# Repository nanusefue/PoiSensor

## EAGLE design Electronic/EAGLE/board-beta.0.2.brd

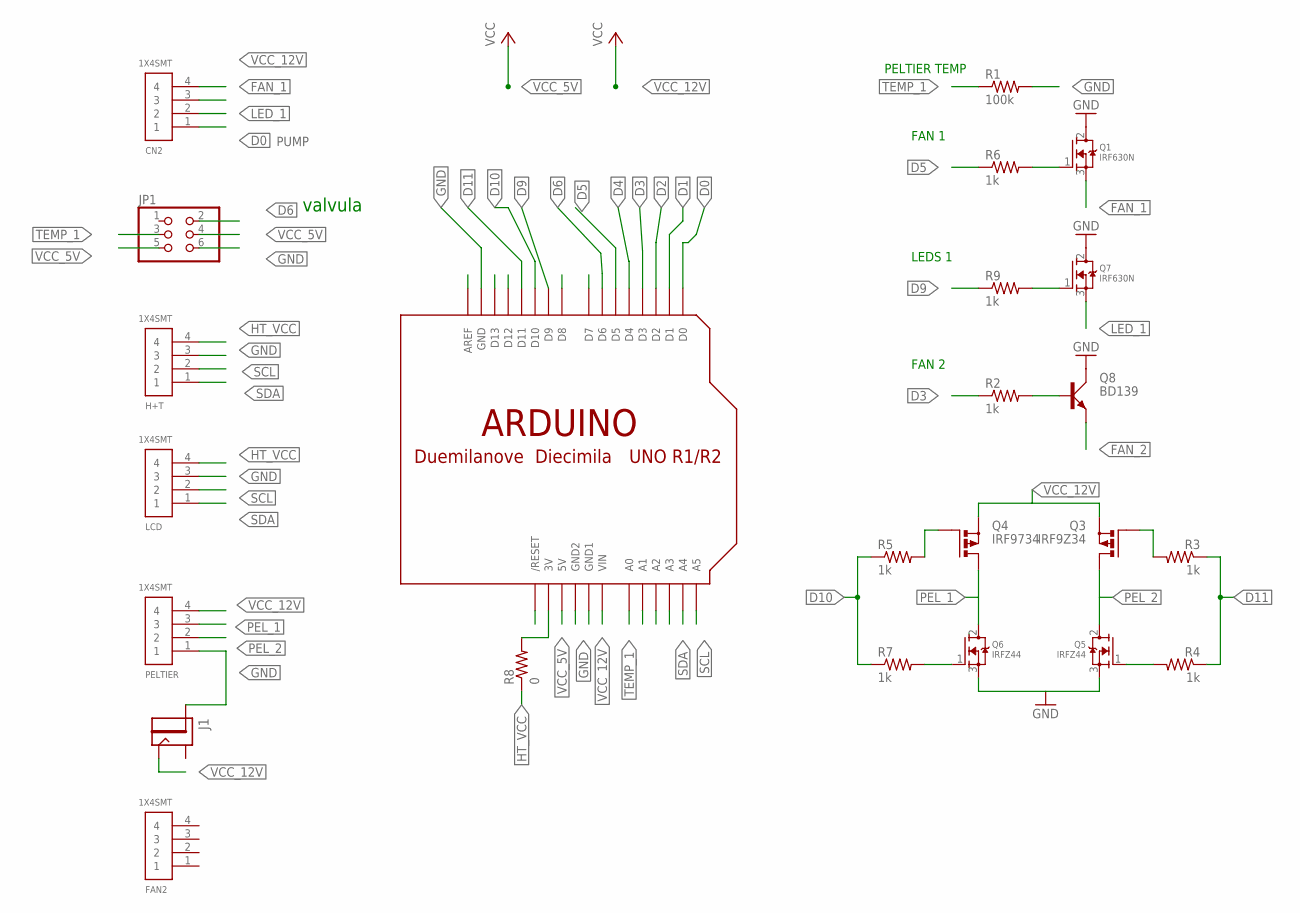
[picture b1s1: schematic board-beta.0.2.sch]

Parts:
CN2: 1X4SMT; 1X4-SMT
FAN2: 1X4SMT; 1X4-SMT
H+T: 1X4SMT; 1X4-SMT
J1: JACK2.1MM; JACK_2.1MM
JP1: PINHD-2X3-SMD; 2X03SMD
LCD: 1X4SMT; 1X4-SMT
PELTIER: 1X4SMT; 1X4-SMT
Q1, Q7: IRF630N; TO220V
Q3: IRF9Z34; TO220BV
Q4: IRF9734; TO220BV
Q5, Q6: IRFZ44; TO220V
Q8: BD139; TO126AV
R1: 100k; R1206FAB
R2, R3, R4, R5, R6, R7, R9: 1k; R1206FAB
R8: 0; R1206FAB
U$1: ARDUINOUNO; ARDUINO

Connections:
D0: CN2.1, U$1.D0
D1: U$1.D1
D2: U$1.D2
D3: R2.1, U$1.D3
D4: U$1.D4
D5: R6.1, U$1.D5
D6: JP1.2, U$1.D6
D9: R9.1, U$1.D9
D10: R5.1, R7.1, U$1.D10
D11: R3.1, R4.1, U$1.D11
FAN_1: CN2.3, Q1.3 (S)
FAN_2: Q8.E
GND: H+T.3, J1.PIN, JP1.6, LCD.3, PELTIER.1, Q1.2 (D), Q5.3 (S), Q6.3 (S), Q7.2 (D), Q8.C, R1.2, U$1.GND, U$1.GND2
HT_VCC: H+T.4, LCD.4, R8.1
LED_1: CN2.2, Q7.3 (S)
unnamed: Q1.1 (G), R6.2
unnamed: Q4.G, R5.2
unnamed: Q3.G, R3.2
unnamed: R8.2, U$1.3V
unnamed: Q5.1 (G), R4.2
unnamed: Q6.1 (G), R7.2
unnamed: Q8.B, R2.2
unnamed: Q7.1 (G), R9.2
PEL_1: PELTIER.3, Q4.D, Q6.2 (D)
PEL_2: PELTIER.2, Q3.D, Q5.2 (D)
SCL: H+T.2, LCD.2, U$1.A5
SDA: H+T.1, LCD.1, U$1.A4
TEMP_1: JP1.3, R1.1, U$1.A0
VCC_5V: JP1.4, JP1.5, U$1.5V
VCC_12V: CN2.4, J1.CONTACT, PELTIER.4, Q3.S, Q4.S, U$1.VIN

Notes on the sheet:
FAN 1
PUMP
valvula
LEDS 1
PELTIER TEMP
FAN 2

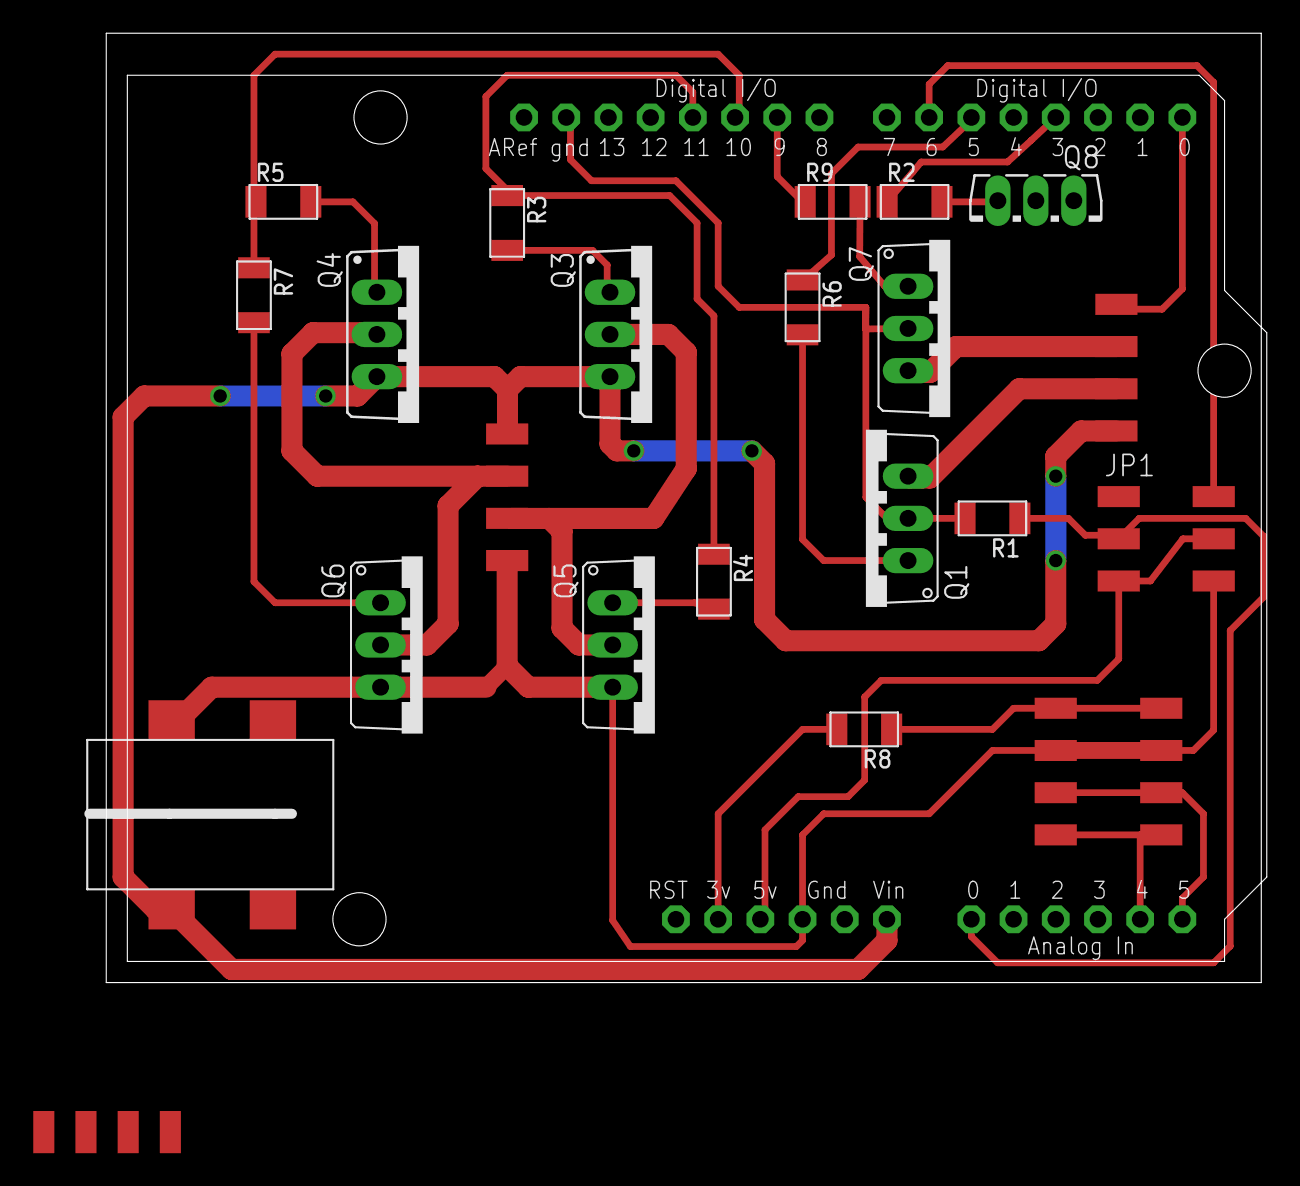
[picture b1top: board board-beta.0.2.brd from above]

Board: 2 copper layers, 69.5 x 57.1 mm, 24 parts (0 on the bottom side), 26 nets.

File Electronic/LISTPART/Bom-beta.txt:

Partlist

Exported from board-beta.sch at 8/1/17 18:01

EAGLE Version 7.7.0 Copyright (c) 1988-2016 CadSoft

Assembly variant: 

Part     Value          Device             Package    Library          Sheet

CN2      1X4SMT         1X4SMT             1X4-SMT    adafruit         1
H+T      1X4SMT         1X4SMT             1X4-SMT    adafruit         1
J1       JACK2.1MM      JACK2.1MM          JACK_2.1MM fab              1
JP1                     PINHD-2X3-SMD      2X03SMD    fab              1
LCD      1X4SMT         1X4SMT             1X4-SMT    adafruit         1
PELTIER  1X4SMT         1X4SMT             1X4-SMT    adafruit         1
Q1       IRF630N        MOSFET-NGDS_TO220V TO220V     adafruit         1
Q3       IRF9Z34        PMOSFET_PTO220BV   TO220BV    transistor-power 1
Q4       IRF9734        PMOSFET_PTO220BV   TO220BV    transistor-power 1
Q5       IRFZ44         MOSFET-NGDS_TO220V TO220V     adafruit         1
Q6       IRFZ44         MOSFET-NGDS_TO220V TO220V     adafruit         1
Q7       IRF630N        MOSFET-NGDS_TO220V TO220V     adafruit         1
R1       100k           RES-US1206FAB      R1206FAB   fab              1
R3       1k             RES-US1206FAB      R1206FAB   fab              1
R4       1k             RES-US1206FAB      R1206FAB   fab              1
R5       1k             RES-US1206FAB      R1206FAB   fab              1
R6       1k             RES-US1206FAB      R1206FAB   fab              1
R7       1k             RES-US1206FAB      R1206FAB   fab              1
R8       0              RES-US1206FAB      R1206FAB   fab              1
R9       1k             RES-US1206FAB      R1206FAB   fab              1
U$1      ARDUINOUNO     ARDUINOUNO         ARDUINO    adafruit         1

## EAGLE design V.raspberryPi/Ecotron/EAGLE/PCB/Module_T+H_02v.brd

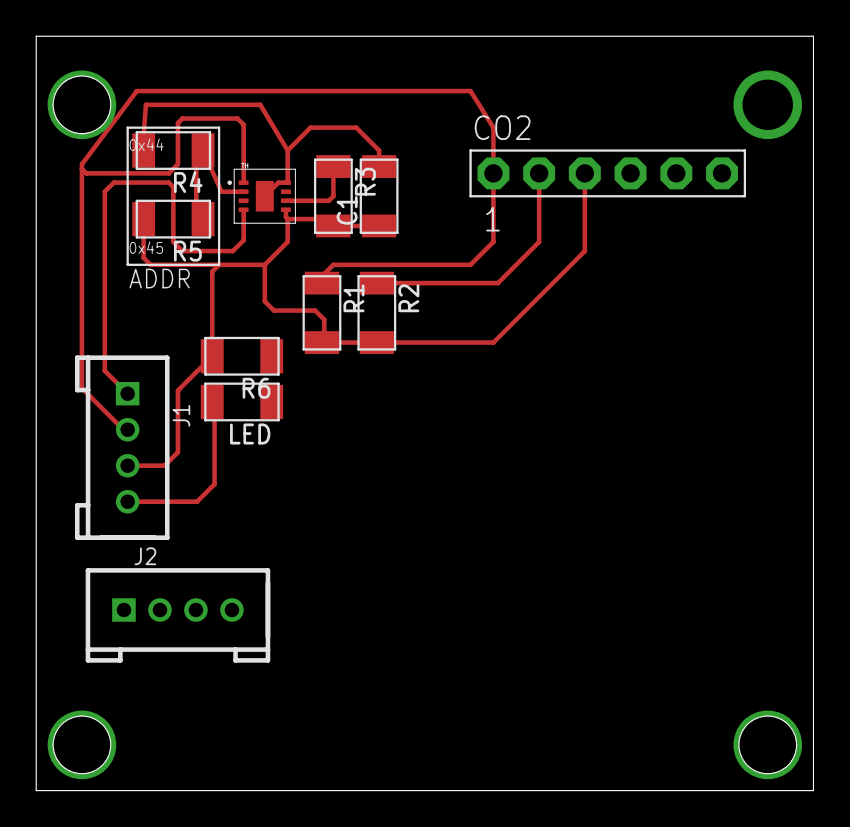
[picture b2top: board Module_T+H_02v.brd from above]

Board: 2 copper layers, 43.2 x 41.9 mm, 12 parts (0 on the bottom side), 7 nets.

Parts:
C1: C1206FAB
CO2: T6713-6H; PINS
J1, J2: 4P-2.0; HW4-2.0
LED: LEDFAB1206; LED1206FAB
R1, R2, R3: 10k; R1206FAB
R4, R5: R1206FAB
R6: 1,5k; R1206FAB
TH: SHT31-DIS; SHT3X

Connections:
ADDR: R4.1, R5.1, TH.P$2
GND: C1.2, CO2.GND, CO2.NC/GND/10K, J1.4, LED.2, R4.2, TH.P$8, TH.PAD
unnamed: LED.1, R6.1
RST: R3.1, TH.P$6
SCL: CO2.RX/SCL, J1.1, R2.1, TH.P$4
SDA: CO2.TX/SDA, J1.2, R1.1, TH.P$1
VCC: C1.1, CO2.VCC, J1.3, R1.2, R2.2, R3.2, R5.2, R6.2, TH.P$5

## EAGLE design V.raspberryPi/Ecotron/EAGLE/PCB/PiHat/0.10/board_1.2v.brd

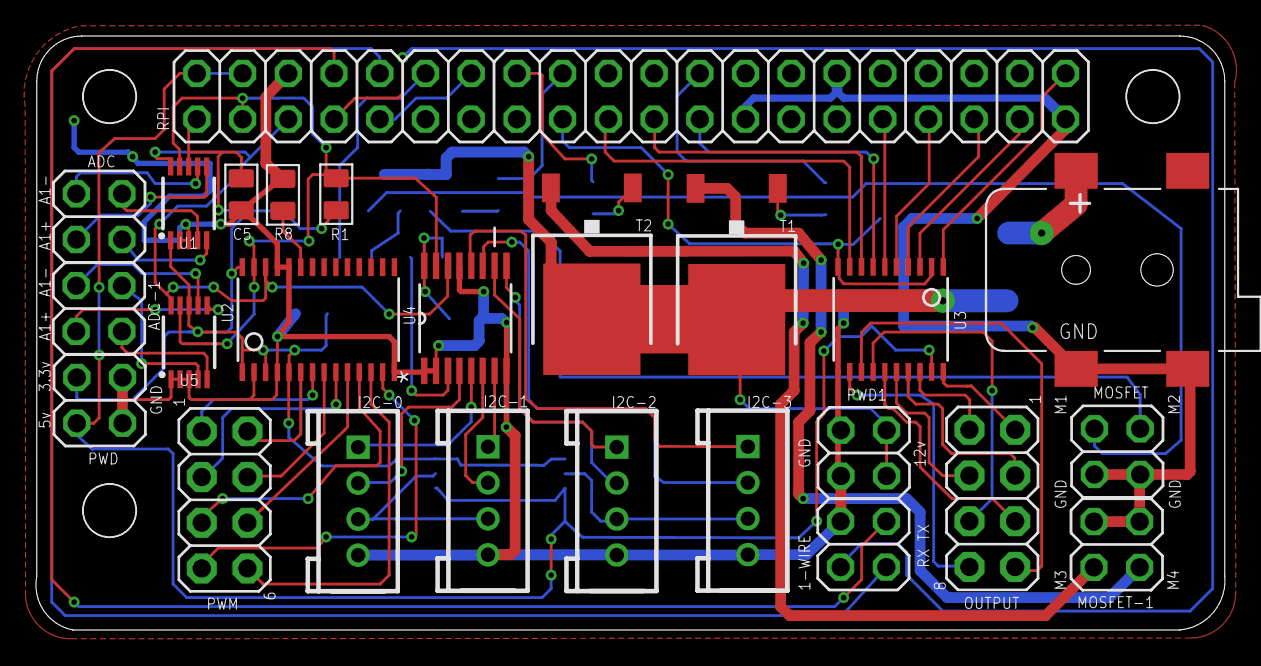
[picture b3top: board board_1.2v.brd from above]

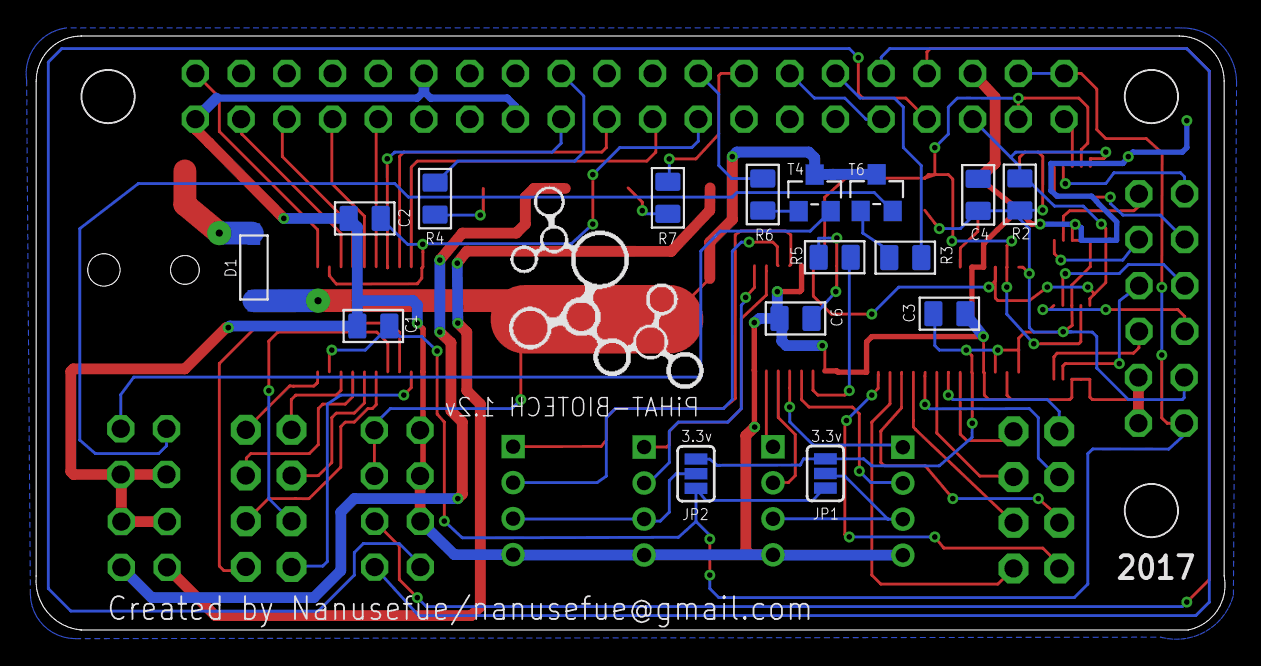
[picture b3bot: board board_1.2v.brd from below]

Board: 2 copper layers, 66.1 x 33.0 mm, 41 parts (16 on the bottom side), 68 nets.

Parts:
1-WIRE: 2X02
ADC: 2X02
ADC-1: 2X02
C1, C2: 1uf; C0805
C3, C5: 100nf; C0805
C4, C6: 10uf; C0805
CN2: DCJACK_2MM_SMT
D1: SOD-123
I2C-0, I2C-1, I2C-2, I2C-3: 4P-2.0; HW4-2.0
JP1, JP2: JUMPER-SMT_3_NO_SILK; SMT-JUMPER_3_NO_SILK
MOSFET: MOSFET; 2X02
MOSFET-1: 2X02
OUTPUT: PINSOUT; 2X04
PWD, PWD1: 2X02
PWM: PWM; 2X04
R1, R2, R3, R4, R5, R6, R7, R8: 10K; R0805
RPI: GPIO; 2X20
T1: T1; TO252
T2: T2; TO252
T4, T6: MOSFET-N; SOT-23
U1, U5: ADS1015; MSOP10
U2: PCA9685; TSSOP28
U3: TXB0108; TSSOP20
U4: PCA9546APW,112; SOP65P640X110-16N

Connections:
1-WIRE: 1-WIRE.2, RPI.7
3,3V: C3.2, C4.1, C5.2, JP1.1, JP2.3, PWD.1, R1.1, R2.1, RPI.1, U1.1, U1.8, U2.1, U2.3, U2.5, U2.28, U5.8
3,3V_1: C2.1, RPI.17, U3.2, U3.10
3,3_1V: C6.1, R5.2, U4.16
5V: C1.1, JP1.3, JP2.1, PWD.3, RPI.2, RPI.4, U3.19
12V: D1.C, PWD1.1, PWD1.3, T1.3, T2.3, T4.3, T6.3
A0+: ADC.3, U1.4
A0+_1: ADC-1.3, U5.4
A0-: ADC.1, U1.5
A0-_1: ADC-1.1, U5.5
A1+: ADC.2, U1.6
A1+_1: ADC-1.2, U5.6
A1-: ADC.4, U1.7
A1-_1: ADC-1.4, U5.7
B1: OUTPUT.7, U3.20
B2: OUTPUT.8, U3.18
B3: OUTPUT.5, U3.17
B4: OUTPUT.6, U3.16
B5: OUTPUT.3, U3.15
B6: OUTPUT.4, U3.14
B7: OUTPUT.1, U3.13
B8: OUTPUT.2, U3.12
GND: 1-WIRE.4, C1.2, C2.2, C3.1, C4.2, C5.1, C6.2, CN2.GND, CN2.GNDBREAK, I2C-0.4, I2C-1.4, I2C-2.4, I2C-3.4, MOSFET.3, MOSFET.4, MOSFET-1.3, MOSFET-1.4, PWD.2, PWD.4, PWD1.2, PWD1.4, R8.1, RPI.6, RPI.9, RPI.14, RPI.25, RPI.30, RPI.39, U1.2, U1.3, U2.2, U2.4, U2.14, U2.24, U2.25, U3.11, U4.1, U4.2, U4.8, U4.13, U5.1, U5.2, U5.3
GPIO6: RPI.31, U3.6
GPIO8: R4.2, RPI.24
GPIO9: RPI.21, U3.8
GPIO10: RPI.19, U3.9
GPIO11: RPI.23, U3.7
GPIO13: RPI.33, U3.5
GPIO18: R3.2, RPI.12
GPIO19: RPI.35, U3.4
GPIO21: RPI.40, U3.1
GPIO23: R7.2, RPI.16
GPIO24: R6.2, RPI.18
GPIO26: RPI.37, U3.3
MOSFET_1: MOSFET.1, T6.2
MOSFET_2: MOSFET.2, T4.2
MOSFET_3: MOSFET-1.2, T2.2
MOSFET_4: MOSFET-1.1, T1.2
unnamed: CN2.PWR1, D1.A
unnamed: R3.1, T6.1
unnamed: R5.1, U4.3
unnamed: R4.1, T1.1
unnamed: R6.1, T4.1
unnamed: R7.1, T2.1
unnamed: R8.2, U2.23
PWM0: PWM.2, U2.6
PWM1: PWM.1, U2.7
PWM2: PWM.4, U2.8
PWM3: PWM.3, U2.9
PWM4: PWM.6, U2.10
PWM5: PWM.5, U2.11
PWM6: PWM.8, U2.12
PWM7: PWM.7, U2.13
RXD: 1-WIRE.1, RPI.10
SC0: I2C-0.1, U4.5
SC1: I2C-1.1, U4.7
SC2: I2C-2.1, U4.10
SC3: I2C-3.1, U4.12
SCL: R2.2, RPI.5, U1.10, U2.26, U4.14, U5.10
SD0: I2C-0.2, U4.4
SD1: I2C-1.2, U4.6
SD2: I2C-2.2, U4.9
SD3: I2C-3.2, U4.11
SDA: R1.2, RPI.3, U1.9, U2.27, U4.15, U5.9
TXD: 1-WIRE.3, RPI.8
VCC_I2C_1: I2C-0.3, I2C-1.3, JP1.2
VCC_I2C_2: I2C-2.3, I2C-3.3, JP2.2

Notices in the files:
parts and their libraries:
SparkFun-IC-Conversion: Licensing: Creative Commons ShareAlike 4.0 International - https://creativecommons.org/licenses/by-sa/4.0
